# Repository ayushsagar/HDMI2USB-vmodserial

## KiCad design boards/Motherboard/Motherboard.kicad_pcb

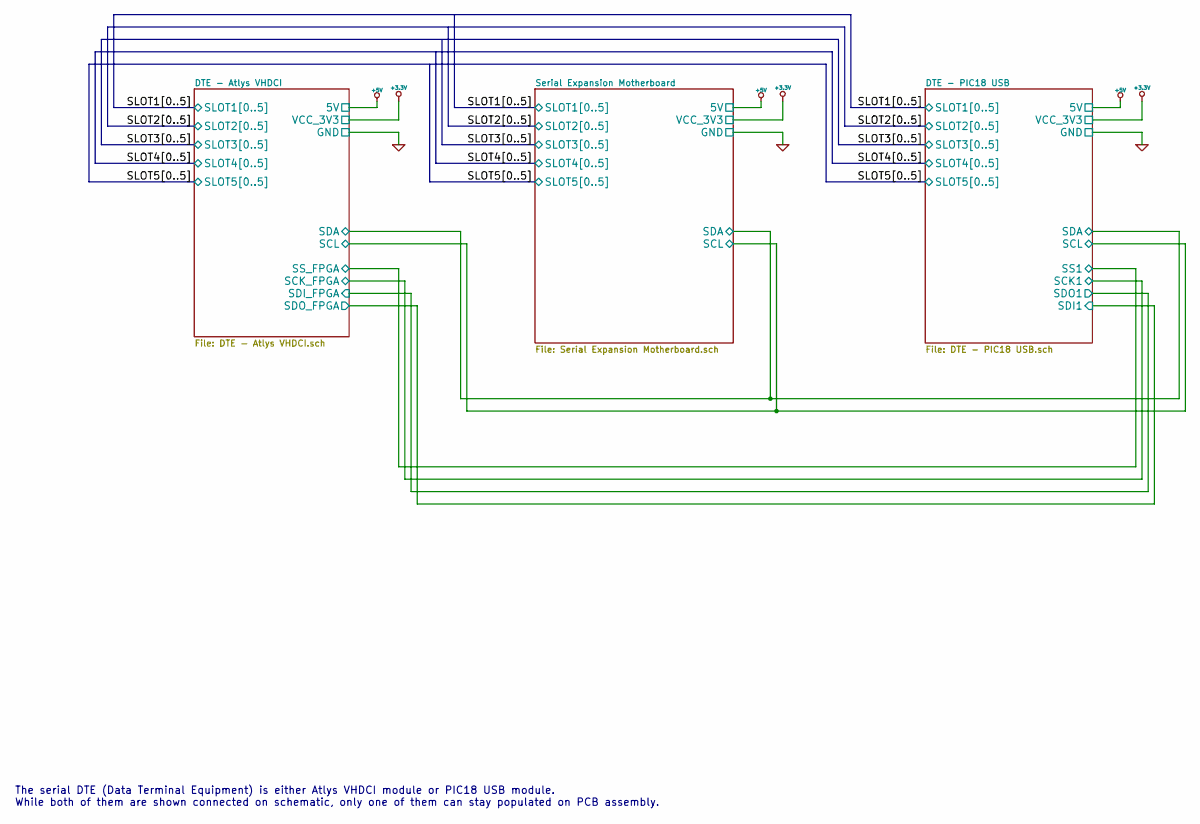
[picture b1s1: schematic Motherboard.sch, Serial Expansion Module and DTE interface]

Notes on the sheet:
The serial DTE (Data Terminal Equipment) is either Atlys VHDCI module or PIC18 USB module. While both of them are shown connected on schematic, only one of them can stay populated on PCB assembly.

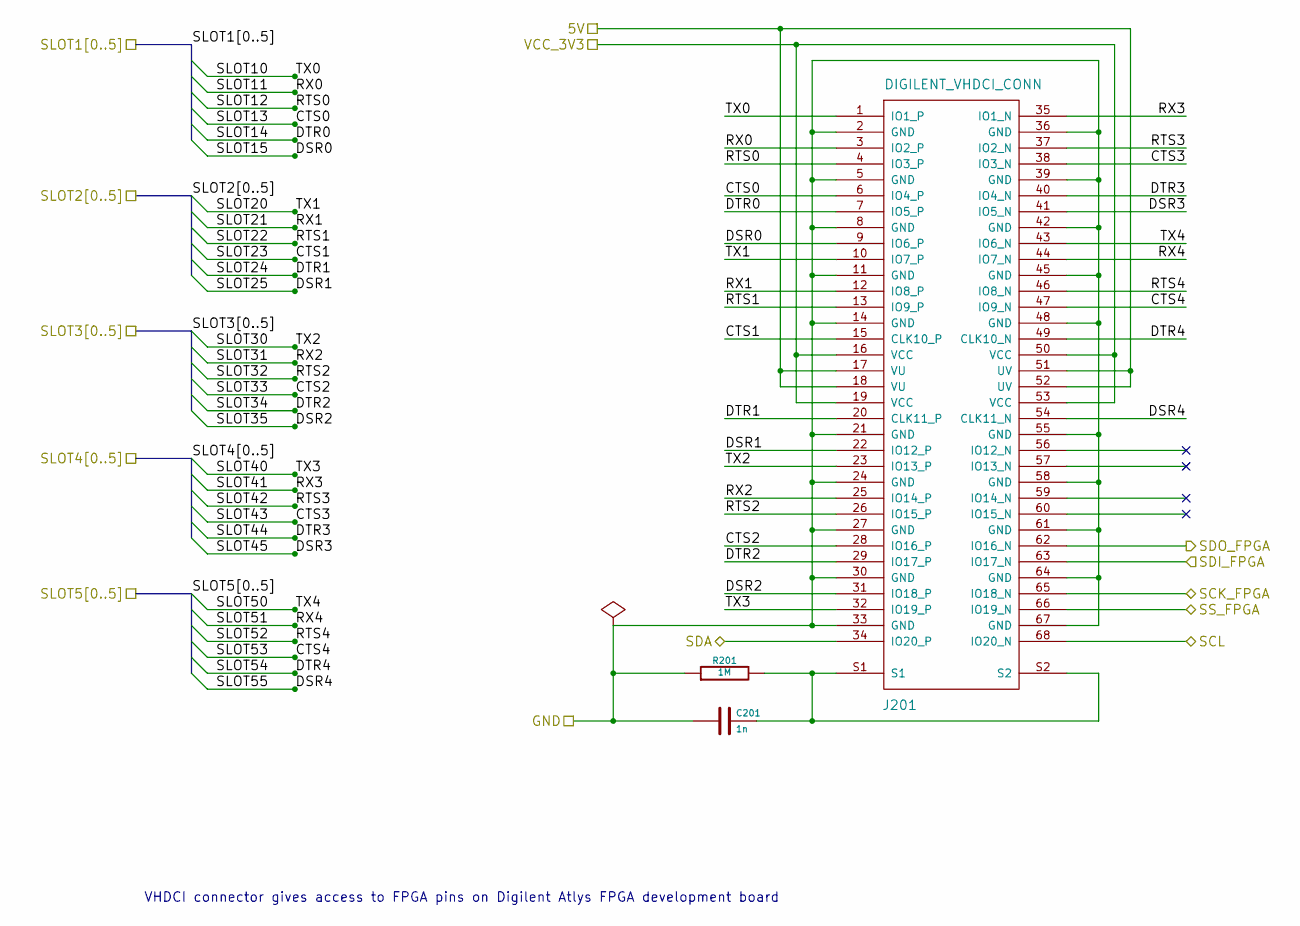
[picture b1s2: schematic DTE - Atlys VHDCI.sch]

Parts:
C201: 1n
J201: DIGILENT_VHDCI_CONN
R201: 1M

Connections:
+3.3V: J201.16 (VCC), J201.19 (VCC), J201.50 (VCC), J201.53 (VCC); also elsewhere on the board
+5V: J201.17 (VU), J201.18 (VU), J201.51 (UV), J201.52 (UV); also elsewhere on the board
/DTE - Atlys VHDCI/SCL: J201.68 (IO20_N); also elsewhere on the board
/DTE - Atlys VHDCI/SDA: J201.34 (IO20_P); also elsewhere on the board
/DTE - Atlys VHDCI/SDI_FPGA: J201.63 (IO17_N); also elsewhere on the board
/DTE - PIC18 USB/SCK1: J201.65 (IO18_N); also elsewhere on the board
/DTE - PIC18 USB/SDI1: J201.62 (IO16_N); also elsewhere on the board
/DTE - PIC18 USB/SS1: J201.66 (IO19_N); also elsewhere on the board
/Serial Expansion Motherboard/Data isolation/IN0_A: J201.1 (IO1_P); also elsewhere on the board
/Serial Expansion Motherboard/Data isolation/IN1_A: J201.4 (IO3_P); also elsewhere on the board
/Serial Expansion Motherboard/Data isolation/IN2_A: J201.7 (IO5_P); also elsewhere on the board
/Serial Expansion Motherboard/Data isolation/IN3_A: J201.10 (IO7_P); also elsewhere on the board
/Serial Expansion Motherboard/Data isolation/IN4_A: J201.13 (IO9_P); also elsewhere on the board
/Serial Expansion Motherboard/Data isolation/IN5_A: J201.20 (CLK11_P); also elsewhere on the board
/Serial Expansion Motherboard/Data isolation/IN6_A: J201.23 (IO13_P); also elsewhere on the board
/Serial Expansion Motherboard/Data isolation/IN7_A: J201.26 (IO15_P); also elsewhere on the board
/Serial Expansion Motherboard/Data isolation/IN8_A: J201.29 (IO17_P); also elsewhere on the board
/Serial Expansion Motherboard/Data isolation/IN9_A: J201.32 (IO19_P); also elsewhere on the board
/Serial Expansion Motherboard/Data isolation/IN10_A: J201.37 (IO2_N); also elsewhere on the board
/Serial Expansion Motherboard/Data isolation/IN11_A: J201.40 (IO4_N); also elsewhere on the board
/Serial Expansion Motherboard/Data isolation/IN12_A: J201.43 (IO6_N); also elsewhere on the board
/Serial Expansion Motherboard/Data isolation/IN13_A: J201.46 (IO8_N); also elsewhere on the board
/Serial Expansion Motherboard/Data isolation/IN14_A: J201.49 (CLK10_N); also elsewhere on the board
/Serial Expansion Motherboard/Data isolation/OUT0_A: J201.3 (IO2_P); also elsewhere on the board
/Serial Expansion Motherboard/Data isolation/OUT1_A: J201.6 (IO4_P); also elsewhere on the board
/Serial Expansion Motherboard/Data isolation/OUT2_A: J201.9 (IO6_P); also elsewhere on the board
/Serial Expansion Motherboard/Data isolation/OUT3_A: J201.12 (IO8_P); also elsewhere on the board
/Serial Expansion Motherboard/Data isolation/OUT4_A: J201.15 (CLK10_P); also elsewhere on the board
/Serial Expansion Motherboard/Data isolation/OUT5_A: J201.22 (IO12_P); also elsewhere on the board
/Serial Expansion Motherboard/Data isolation/OUT6_A: J201.25 (IO14_P); also elsewhere on the board
/Serial Expansion Motherboard/Data isolation/OUT7_A: J201.28 (IO16_P); also elsewhere on the board
/Serial Expansion Motherboard/Data isolation/OUT8_A: J201.31 (IO18_P); also elsewhere on the board
/Serial Expansion Motherboard/Data isolation/OUT9_A: J201.35 (IO1_N); also elsewhere on the board
/Serial Expansion Motherboard/Data isolation/OUT10_A: J201.38 (IO3_N); also elsewhere on the board
/Serial Expansion Motherboard/Data isolation/OUT11_A: J201.41 (IO5_N); also elsewhere on the board
/Serial Expansion Motherboard/Data isolation/OUT12_A: J201.44 (IO7_N); also elsewhere on the board
/Serial Expansion Motherboard/Data isolation/OUT13_A: J201.47 (IO9_N); also elsewhere on the board
/Serial Expansion Motherboard/Data isolation/OUT14_A: J201.54 (CLK11_N); also elsewhere on the board
GND: C201.1, J201.2 (GND), J201.5 (GND), J201.8 (GND), J201.11 (GND), J201.14 (GND), J201.21 (GND), J201.24 (GND), J201.27 (GND), J201.30 (GND), J201.33 (GND), J201.36 (GND), J201.39 (GND), J201.42 (GND), J201.45 (GND), J201.48 (GND), J201.55 (GND), J201.58 (GND), J201.61 (GND), J201.64 (GND), J201.67 (GND), R201.1; also elsewhere on the board
unnamed: C201.2, J201.S1, J201.S2, R201.2

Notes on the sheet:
VHDCI connector gives access to FPGA pins on Digilent Atlys FPGA development board

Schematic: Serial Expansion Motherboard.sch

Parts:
C401: 0.1u
R401, R402: 2.2k
R403: 50
U401: 24AA014

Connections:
+3.3V: R401.1, R402.1, R403.1; also elsewhere on the board
/DTE - Atlys VHDCI/SCL: R402.2, U401.5 (SDA); also elsewhere on the board
/DTE - Atlys VHDCI/SDA: R401.2, U401.6 (SCL); also elsewhere on the board
GND: C401.1, U401.1 (A0), U401.2 (A1), U401.3 (A2), U401.4 (GND), U401.7 (WP); also elsewhere on the board
unnamed: C401.2, R403.2, U401.8 (VCC)

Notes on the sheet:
Motherboard ID EEPROM address set to 0 (000) by shorting A0, A1 and A2 to ground.

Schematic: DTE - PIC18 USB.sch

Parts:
C613, C614: 22p
C615, C616, C618, C619, C620, C623: 0.1u
C617: 10u
C621: 4.7n
C622: 4.7u
D611, D612, D613: LED
DS11, DS12, DS21, DS22, DS31, DS32, DS41, DS42, DS51, DS52: LED
J601: USB
P601: ICSP
P602: SPI2
R619: 10K
R620, R621: 50
R640: 1M
R641: 0.47
R688, R689, R690: 680
R691: 0.10
RS11, RS12, RS21, RS22, RS31, RS32, RS41, RS42, RS51, RS52: 680
U607: PIC18F85J94
U608: AAT3221IGV-3.3-T1
X601: XTAL

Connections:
+3.3V: C616.1, C618.1, C619.1, C620.1, C623.1, P601.2, P602.1, R619.1, R691.2, U607.23 (VUSB3V3), U607.32 (VDD), U607.48 (VDD), U607.71 (VDD); also elsewhere on the board
+5V: C622.1, R641.2, U608.1 (IN), U608.3 (EN); also elsewhere on the board
/DTE - Atlys VHDCI/SCL: U607.44 (RC3/SCL1); also elsewhere on the board
/DTE - Atlys VHDCI/SDA: U607.45 (RC4/SDA1); also elsewhere on the board
/DTE - Atlys VHDCI/SDI_FPGA: U607.3 (RE1); also elsewhere on the board
/DTE - PIC18 USB/LED_P: R688.1, U607.72 (RD0)
/DTE - PIC18 USB/LED_Q: R689.1, U607.18 (RF2)
/DTE - PIC18 USB/LED_R: R690.1, U607.15 (RF5)
/DTE - PIC18 USB/PGC: P601.5, U607.52 (RB6/PGC)
/DTE - PIC18 USB/PGD: P601.4, U607.47 (RB7/PGD)
/DTE - PIC18 USB/SCK1: U607.6 (RG1); also elsewhere on the board
/DTE - PIC18 USB/SCK2_HEADER: P602.4, U607.7 (RG2)
/DTE - PIC18 USB/SDI1: U607.4 (RE0); also elsewhere on the board
/DTE - PIC18 USB/SDI2_HEADER: P602.3, U607.69 (RD1)
/DTE - PIC18 USB/SDO2_HEADER: P602.2, U607.10 (RG4)
/DTE - PIC18 USB/SLOT1_LED1: RS11.1, U607.36 (RC0)
/DTE - PIC18 USB/SLOT1_LED2: RS12.1, U607.35 (RC1)
/DTE - PIC18 USB/SLOT2_LED1: RS21.1, U607.43 (RC2)
/DTE - PIC18 USB/SLOT2_LED2: RS22.1, U607.46 (RC5)
/DTE - PIC18 USB/SLOT3_LED1: RS31.1, U607.37 (RC6)
/DTE - PIC18 USB/SLOT3_LED2: RS32.1, U607.38 (RC7)
/DTE - PIC18 USB/SLOT4_LED1: RS41.1, U607.14 (RF6)
/DTE - PIC18 USB/SLOT4_LED2: RS42.1, U607.13 (RF7)
/DTE - PIC18 USB/SLOT5_LED1: RS51.1, U607.20 (RH6)
/DTE - PIC18 USB/SLOT5_LED2: RS52.1, U607.19 (RH7)
/DTE - PIC18 USB/SS1: U607.5 (RG0); also elsewhere on the board
/DTE - PIC18 USB/SS2_HEADER: P602.5, U607.8 (RG3)
/Serial Expansion Motherboard/Data isolation/IN0_A: U607.28 (RA2); also elsewhere on the board
/Serial Expansion Motherboard/Data isolation/IN1_A: U607.34 (RA4); also elsewhere on the board
/Serial Expansion Motherboard/Data isolation/IN2_A: U607.30 (RA0); also elsewhere on the board
/Serial Expansion Motherboard/Data isolation/IN3_A: U607.55 (RB3); also elsewhere on the board
/Serial Expansion Motherboard/Data isolation/IN4_A: U607.54 (RB4); also elsewhere on the board
/Serial Expansion Motherboard/Data isolation/IN5_A: U607.58 (RB0); also elsewhere on the board
/Serial Expansion Motherboard/Data isolation/IN6_A: U607.65 (RD5/SDA2); also elsewhere on the board
/Serial Expansion Motherboard/Data isolation/IN7_A: U607.64 (RD6/SCL2); also elsewhere on the board
/Serial Expansion Motherboard/Data isolation/IN8_A: U607.68 (RD2); also elsewhere on the board
/Serial Expansion Motherboard/Data isolation/IN9_A: U607.75 (RE5); also elsewhere on the board
/Serial Expansion Motherboard/Data isolation/IN10_A: U607.74 (RE6); also elsewhere on the board
/Serial Expansion Motherboard/Data isolation/IN11_A: U607.78 (RE2); also elsewhere on the board
/Serial Expansion Motherboard/Data isolation/IN12_A: U607.1 (RH2); also elsewhere on the board
/Serial Expansion Motherboard/Data isolation/IN13_A: U607.22 (RH4); also elsewhere on the board
/Serial Expansion Motherboard/Data isolation/IN14_A: U607.79 (RH0); also elsewhere on the board
/Serial Expansion Motherboard/Data isolation/OUT0_A: U607.27 (RA3); also elsewhere on the board
/Serial Expansion Motherboard/Data isolation/OUT1_A: U607.33 (RA5); also elsewhere on the board
/Serial Expansion Motherboard/Data isolation/OUT2_A: U607.29 (RA1); also elsewhere on the board
/Serial Expansion Motherboard/Data isolation/OUT3_A: U607.56 (RB2); also elsewhere on the board
/Serial Expansion Motherboard/Data isolation/OUT4_A: U607.53 (RB5); also elsewhere on the board
/Serial Expansion Motherboard/Data isolation/OUT5_A: U607.57 (RB1); also elsewhere on the board
/Serial Expansion Motherboard/Data isolation/OUT6_A: U607.66 (RD4); also elsewhere on the board
/Serial Expansion Motherboard/Data isolation/OUT7_A: U607.63 (RD7); also elsewhere on the board
/Serial Expansion Motherboard/Data isolation/OUT8_A: U607.67 (RD3); also elsewhere on the board
/Serial Expansion Motherboard/Data isolation/OUT9_A: U607.76 (RE4); also elsewhere on the board
/Serial Expansion Motherboard/Data isolation/OUT10_A: U607.73 (RE7); also elsewhere on the board
/Serial Expansion Motherboard/Data isolation/OUT11_A: U607.77 (RE3); also elsewhere on the board
/Serial Expansion Motherboard/Data isolation/OUT12_A: U607.2 (RH3); also elsewhere on the board
/Serial Expansion Motherboard/Data isolation/OUT13_A: U607.21 (RH5); also elsewhere on the board
/Serial Expansion Motherboard/Data isolation/OUT14_A: U607.80 (RH1); also elsewhere on the board
GND: C613.1, C614.2, C615.2, C616.2, C617.2, C618.2, C619.2, C620.2, C621.2, C622.2, C623.2, D611.2 (K), D612.2 (K), D613.2 (K), DS11.2 (K), DS12.2 (K), DS21.2 (K), DS22.2 (K), DS31.2 (K), DS32.2 (K), DS41.2 (K), DS42.2 (K), DS51.2 (K), DS52.2 (K), J601.4 (GND), P601.3, P602.6, R640.2, U607.11 (VSS), U607.26 (AVSS), U607.31 (VSS), U607.51 (VSS), U607.70 (VSS), U608.2 (GND); also elsewhere on the board
unnamed: D613.1 (A), R690.2
unnamed: D612.1 (A), R689.2
unnamed: DS52.1 (A), RS52.2
unnamed: D611.1 (A), R688.2
unnamed: R621.1, U607.17 (D-/RF3)
unnamed: DS51.1 (A), RS51.2
unnamed: R620.1, U607.16 (D+/RF4)
unnamed: J601.3 (D+), R620.2
unnamed: J601.2 (D-), R621.2
unnamed: J601.1 (Vbus), R641.1
unnamed: R691.1, U608.5 (OUT)
unnamed: DS11.1 (A), RS11.2
unnamed: C621.1, J601.5 (Shield_1), J601.6 (Shield_2), R640.1
unnamed: DS12.1 (A), RS12.2
unnamed: P601.1, R619.2, U607.9 (~MCLR)
unnamed: C617.1, U607.12 (VCAP)
unnamed: C615.1, U607.25 (AVDD)
unnamed: DS41.1 (A), RS41.2
unnamed: C613.2, U607.50 (RA6/OSC1), X601.2
unnamed: C614.1, U607.49 (RA7/OSC2), X601.1
unnamed: DS42.1 (A), RS42.2
unnamed: DS32.1 (A), RS32.2
unnamed: DS31.1 (A), RS31.2
unnamed: DS22.1 (A), RS22.2
unnamed: DS21.1 (A), RS21.2

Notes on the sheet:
PIC18F85J94 MCU simulates production board for HDMI2USB as well as enables standalone operation using USB interface.
- First 4 serial ports use the 4 available hardware UARTs. Remaining serial ports need to be bitbanged - Crystal (and capactors) is optional. PIC18F85J94 has FRC internal clock, which is accurate enough to support USB 2.0 and UART.

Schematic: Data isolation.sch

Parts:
C601, C602, C603, C604, C605, C606, C607, C608, C609, C610, C611, C612: 0.1u
R601, R608, R615, R622, R629, R636, R643, R650, R657, R664, R671, R678: 50
R602, R603, R604, R605, R606, R607, R609, R610, R611, R612, R613, R614, R616, R617, R618, R623, R624, R625, R626, R627, R628, R630, R631, R632, R633, R634, R635, R637, R638, R639, R644, R645, R646, R647, R648, R649, R651, R652, R653, R654, R655, R656, R658, R659, R660, R665, R666, R667, R668, R669, R670, R672, R673, R674, R675, R676, R677, R679, R680, R681: 100
U601, U602, U603, U604: SI8660
U605, U606: SI8630/SI8660

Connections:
+3.3V: R601.1, R608.1, R615.1, R664.2, R671.2, R678.2; also elsewhere on the board
+5V_ISO: R622.2, R629.2, R636.2, R643.1, R650.1, R657.1; also elsewhere on the board
/Serial Expansion Motherboard/Data isolation/IN0_A: R602.1; also elsewhere on the board
/Serial Expansion Motherboard/Data isolation/IN0_B: R644.1; also elsewhere on the board
/Serial Expansion Motherboard/Data isolation/IN1_A: R603.1; also elsewhere on the board
/Serial Expansion Motherboard/Data isolation/IN2_A: R604.1; also elsewhere on the board
/Serial Expansion Motherboard/Data isolation/IN3_A: R605.1; also elsewhere on the board
/Serial Expansion Motherboard/Data isolation/IN3_B: R647.1; also elsewhere on the board
/Serial Expansion Motherboard/Data isolation/IN4_A: R606.1; also elsewhere on the board
/Serial Expansion Motherboard/Data isolation/IN5_A: R607.1; also elsewhere on the board
/Serial Expansion Motherboard/Data isolation/IN6_A: R609.1; also elsewhere on the board
/Serial Expansion Motherboard/Data isolation/IN6_B: R651.1; also elsewhere on the board
/Serial Expansion Motherboard/Data isolation/IN7_A: R610.1; also elsewhere on the board
/Serial Expansion Motherboard/Data isolation/IN8_A: R611.1; also elsewhere on the board
/Serial Expansion Motherboard/Data isolation/IN9_A: R612.1; also elsewhere on the board
/Serial Expansion Motherboard/Data isolation/IN9_B: R654.1; also elsewhere on the board
/Serial Expansion Motherboard/Data isolation/IN10_A: R613.1; also elsewhere on the board
/Serial Expansion Motherboard/Data isolation/IN11_A: R614.1; also elsewhere on the board
/Serial Expansion Motherboard/Data isolation/IN12_A: R616.1; also elsewhere on the board
/Serial Expansion Motherboard/Data isolation/IN12_B: R658.1; also elsewhere on the board
/Serial Expansion Motherboard/Data isolation/IN13_A: R617.1; also elsewhere on the board
/Serial Expansion Motherboard/Data isolation/IN14_A: R618.1; also elsewhere on the board
/Serial Expansion Motherboard/Data isolation/OUT0_A: R665.2; also elsewhere on the board
/Serial Expansion Motherboard/Data isolation/OUT0_B: R623.2; also elsewhere on the board
/Serial Expansion Motherboard/Data isolation/OUT1_A: R666.2; also elsewhere on the board
/Serial Expansion Motherboard/Data isolation/OUT1_B: R624.2; also elsewhere on the board
/Serial Expansion Motherboard/Data isolation/OUT2_A: R667.2; also elsewhere on the board
/Serial Expansion Motherboard/Data isolation/OUT3_A: R668.2; also elsewhere on the board
/Serial Expansion Motherboard/Data isolation/OUT3_B: R626.2; also elsewhere on the board
/Serial Expansion Motherboard/Data isolation/OUT4_A: R669.2; also elsewhere on the board
/Serial Expansion Motherboard/Data isolation/OUT4_B: R627.2; also elsewhere on the board
/Serial Expansion Motherboard/Data isolation/OUT5_A: R670.2; also elsewhere on the board
/Serial Expansion Motherboard/Data isolation/OUT6_A: R672.2; also elsewhere on the board
/Serial Expansion Motherboard/Data isolation/OUT6_B: R630.2; also elsewhere on the board
/Serial Expansion Motherboard/Data isolation/OUT7_A: R673.2; also elsewhere on the board
/Serial Expansion Motherboard/Data isolation/OUT8_A: R674.2; also elsewhere on the board
/Serial Expansion Motherboard/Data isolation/OUT9_A: R675.2; also elsewhere on the board
/Serial Expansion Motherboard/Data isolation/OUT9_B: R633.2; also elsewhere on the board
/Serial Expansion Motherboard/Data isolation/OUT10_A: R676.2; also elsewhere on the board
/Serial Expansion Motherboard/Data isolation/OUT10_B: R634.2; also elsewhere on the board
/Serial Expansion Motherboard/Data isolation/OUT11_A: R677.2; also elsewhere on the board
/Serial Expansion Motherboard/Data isolation/OUT12_A: R679.2; also elsewhere on the board
/Serial Expansion Motherboard/Data isolation/OUT12_B: R637.2; also elsewhere on the board
/Serial Expansion Motherboard/Data isolation/OUT13_A: R680.2; also elsewhere on the board
/Serial Expansion Motherboard/Data isolation/OUT13_B: R638.2; also elsewhere on the board
/Serial Expansion Motherboard/Data isolation/OUT14_A: R681.2; also elsewhere on the board
/Serial Expansion Motherboard/Daughterboard slots/CTS0_ISO: R645.1; also elsewhere on the board
/Serial Expansion Motherboard/Daughterboard slots/CTS1_ISO: R648.1; also elsewhere on the board
/Serial Expansion Motherboard/Daughterboard slots/CTS2_ISO: R631.2, R652.1; also elsewhere on the board
/Serial Expansion Motherboard/Daughterboard slots/CTS3_ISO: R655.1; also elsewhere on the board
/Serial Expansion Motherboard/Daughterboard slots/CTS4_ISO: R659.1; also elsewhere on the board
/Serial Expansion Motherboard/Daughterboard slots/DSR0_ISO: R646.1; also elsewhere on the board
/Serial Expansion Motherboard/Daughterboard slots/DSR1_ISO: R649.1; also elsewhere on the board
/Serial Expansion Motherboard/Daughterboard slots/DSR2_ISO: R653.1; also elsewhere on the board
/Serial Expansion Motherboard/Daughterboard slots/DSR3_ISO: R656.1; also elsewhere on the board
/Serial Expansion Motherboard/Daughterboard slots/DSR4_ISO: R660.1; also elsewhere on the board
/Serial Expansion Motherboard/Daughterboard slots/DTR0_ISO: R625.2; also elsewhere on the board
/Serial Expansion Motherboard/Daughterboard slots/DTR1_ISO: R628.2; also elsewhere on the board
/Serial Expansion Motherboard/Daughterboard slots/DTR2_ISO: R632.2; also elsewhere on the board
/Serial Expansion Motherboard/Daughterboard slots/DTR3_ISO: R635.2; also elsewhere on the board
/Serial Expansion Motherboard/Daughterboard slots/DTR4_ISO: R639.2; also elsewhere on the board
GND: C601.2, C602.2, C603.2, C610.2, C611.2, C612.2, U601.8 (GND1), U602.9 (GND2), U603.8 (GND1), U604.9 (GND2), U605.8 (GND1), U606.9 (GND2); also elsewhere on the board
GND_ISO: C604.2, C605.2, C606.2, C607.2, C608.2, C609.2, U601.9 (GND2), U602.8 (GND1), U603.9 (GND2), U604.8 (GND1), U605.9 (GND2), U606.8 (GND1); also elsewhere on the board
unnamed: R677.1, U604.10 (B6)
unnamed: R676.1, U604.11 (B5)
unnamed: R675.1, U604.12 (B4)
unnamed: R674.1, U604.13 (B3)
unnamed: R673.1, U604.14 (B2)
unnamed: R672.1, U604.15 (B1)
unnamed: R605.2, U601.5 (A4)
unnamed: R611.2, U603.4 (A3)
unnamed: R610.2, U603.3 (A2)
unnamed: R609.2, U603.2 (A1)
unnamed: R614.2, U603.7 (A6)
unnamed: R606.2, U601.6 (A5)
unnamed: R604.2, U601.4 (A3)
unnamed: R603.2, U601.3 (A2)
unnamed: R602.2, U601.2 (A1)
unnamed: R607.2, U601.7 (A6)
unnamed: R631.1, U603.14 (B2)
unnamed: R638.1, U605.13 (B3)
unnamed: R637.1, U605.14 (B2)
unnamed: R635.1, U603.10 (B6)
unnamed: R633.1, U603.12 (B4)
unnamed: R632.1, U603.13 (B3)
unnamed: R630.1, U603.15 (B1)
unnamed: R618.2, U605.5 (A4)
unnamed: R617.2, U605.4 (A3)
unnamed: R616.2, U605.3 (A2)
unnamed: R653.2, U604.4 (A3)
unnamed: R660.2, U606.5 (A4)
unnamed: R659.2, U606.4 (A3)
unnamed: R658.2, U606.3 (A2)
unnamed: R656.2, U604.7 (A6)
unnamed: R655.2, U604.6 (A5)
unnamed: R654.2, U604.5 (A4)
unnamed: R612.2, U603.5 (A4)
unnamed: R652.2, U604.3 (A2)
unnamed: R651.2, U604.2 (A1)
unnamed: R639.1, U605.12 (B4)
unnamed: R665.1, U602.15 (B1)
unnamed: R666.1, U602.14 (B2)
unnamed: R667.1, U602.13 (B3)
unnamed: R668.1, U602.12 (B4)
unnamed: R669.1, U602.11 (B5)
unnamed: R670.1, U602.10 (B6)
unnamed: R625.1, U601.13 (B3)
unnamed: R628.1, U601.10 (B6)
unnamed: R627.1, U601.11 (B5)
unnamed: R626.1, U601.12 (B4)
unnamed: R624.1, U601.14 (B2)
unnamed: R623.1, U601.15 (B1)
unnamed: R613.2, U603.6 (A5)
unnamed: R644.2, U602.2 (A1)
unnamed: R645.2, U602.3 (A2)
unnamed: R646.2, U602.4 (A3)
unnamed: R647.2, U602.5 (A4)
unnamed: R648.2, U602.6 (A5)
unnamed: R649.2, U602.7 (A6)
unnamed: R679.1, U606.14 (B2)
unnamed: R680.1, U606.13 (B3)
unnamed: R681.1, U606.12 (B4)
unnamed: R634.1, U603.11 (B5)
unnamed: C608.1, R650.2, U604.1 (VDD1)
unnamed: C612.1, R678.1, U606.16 (VDD2)
unnamed: C609.1, R657.2, U606.1 (VDD1)
unnamed: C607.1, R643.2, U602.1 (VDD1)
unnamed: C606.1, R636.1, U605.16 (VDD2)
unnamed: C610.1, R664.1, U602.16 (VDD2)
unnamed: C611.1, R671.1, U604.16 (VDD2)
unnamed: C604.1, R622.1, U601.16 (VDD2)
unnamed: C602.1, R608.2, U603.1 (VDD1)
unnamed: C601.1, R601.2, U601.1 (VDD1)
unnamed: C605.1, R629.1, U603.16 (VDD2)
unnamed: C603.1, R615.2, U605.1 (VDD1)

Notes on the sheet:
Postfix A refers to DTE side and postfix B refers to daughterboard side. e.g. IN12_A in an input from DTE side and OUT12_B is the output connected to daughterboard side.

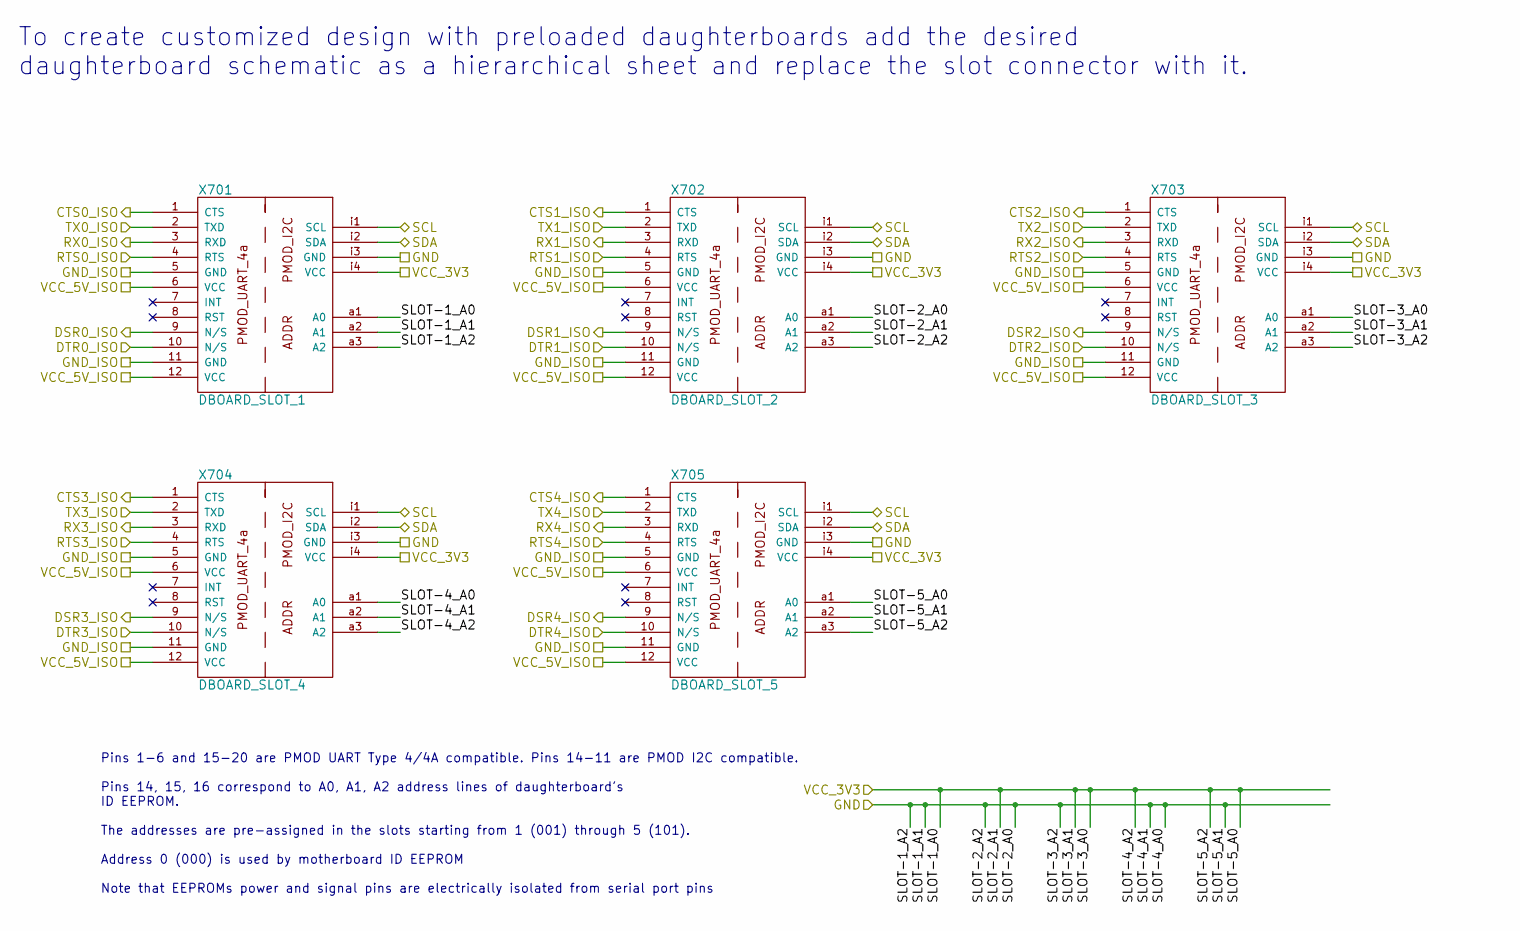
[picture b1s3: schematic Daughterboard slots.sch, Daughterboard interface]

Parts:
X701: DBOARD_SLOT_1
X702: DBOARD_SLOT_2
X703: DBOARD_SLOT_3
X704: DBOARD_SLOT_4
X705: DBOARD_SLOT_5

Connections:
+3.3V: X701.a1 (A0), X701.i4 (VCC), X702.a2 (A1), X702.i4 (VCC), X703.a1 (A0), X703.a2 (A1), X703.i4 (VCC), X704.a3 (A2), X704.i4 (VCC), X705.a1 (A0), X705.a3 (A2), X705.i4 (VCC); also elsewhere on the board
+5V_ISO: X701.6 (VCC), X701.12 (VCC), X702.6 (VCC), X702.12 (VCC), X703.6 (VCC), X703.12 (VCC), X704.6 (VCC), X704.12 (VCC), X705.6 (VCC), X705.12 (VCC); also elsewhere on the board
/DTE - Atlys VHDCI/SCL: X701.i2 (SDA), X702.i2 (SDA), X703.i2 (SDA), X704.i2 (SDA), X705.i2 (SDA); also elsewhere on the board
/DTE - Atlys VHDCI/SDA: X701.i1 (SCL), X702.i1 (SCL), X703.i1 (SCL), X704.i1 (SCL), X705.i1 (SCL); also elsewhere on the board
/Serial Expansion Motherboard/Data isolation/IN0_B: X701.3 (RXD); also elsewhere on the board
/Serial Expansion Motherboard/Data isolation/IN3_B: X702.3 (RXD); also elsewhere on the board
/Serial Expansion Motherboard/Data isolation/IN6_B: X703.3 (RXD); also elsewhere on the board
/Serial Expansion Motherboard/Data isolation/IN9_B: X704.3 (RXD); also elsewhere on the board
/Serial Expansion Motherboard/Data isolation/IN12_B: X705.3 (RXD); also elsewhere on the board
/Serial Expansion Motherboard/Data isolation/OUT0_B: X701.2 (TXD); also elsewhere on the board
/Serial Expansion Motherboard/Data isolation/OUT1_B: X701.4 (RTS); also elsewhere on the board
/Serial Expansion Motherboard/Data isolation/OUT3_B: X702.2 (TXD); also elsewhere on the board
/Serial Expansion Motherboard/Data isolation/OUT4_B: X702.4 (RTS); also elsewhere on the board
/Serial Expansion Motherboard/Data isolation/OUT6_B: X703.2 (TXD); also elsewhere on the board
/Serial Expansion Motherboard/Data isolation/OUT9_B: X704.2 (TXD); also elsewhere on the board
/Serial Expansion Motherboard/Data isolation/OUT10_B: X704.4 (RTS); also elsewhere on the board
/Serial Expansion Motherboard/Data isolation/OUT12_B: X705.2 (TXD); also elsewhere on the board
/Serial Expansion Motherboard/Data isolation/OUT13_B: X705.4 (RTS); also elsewhere on the board
/Serial Expansion Motherboard/Daughterboard slots/CTS0_ISO: X701.1 (CTS); also elsewhere on the board
/Serial Expansion Motherboard/Daughterboard slots/CTS1_ISO: X702.1 (CTS); also elsewhere on the board
/Serial Expansion Motherboard/Daughterboard slots/CTS2_ISO: X703.1 (CTS), X703.4 (RTS); also elsewhere on the board
/Serial Expansion Motherboard/Daughterboard slots/CTS3_ISO: X704.1 (CTS); also elsewhere on the board
/Serial Expansion Motherboard/Daughterboard slots/CTS4_ISO: X705.1 (CTS); also elsewhere on the board
/Serial Expansion Motherboard/Daughterboard slots/DSR0_ISO: X701.9 (N/S); also elsewhere on the board
/Serial Expansion Motherboard/Daughterboard slots/DSR1_ISO: X702.9 (N/S); also elsewhere on the board
/Serial Expansion Motherboard/Daughterboard slots/DSR2_ISO: X703.9 (N/S); also elsewhere on the board
/Serial Expansion Motherboard/Daughterboard slots/DSR3_ISO: X704.9 (N/S); also elsewhere on the board
/Serial Expansion Motherboard/Daughterboard slots/DSR4_ISO: X705.9 (N/S); also elsewhere on the board
/Serial Expansion Motherboard/Daughterboard slots/DTR0_ISO: X701.10 (N/S); also elsewhere on the board
/Serial Expansion Motherboard/Daughterboard slots/DTR1_ISO: X702.10 (N/S); also elsewhere on the board
/Serial Expansion Motherboard/Daughterboard slots/DTR2_ISO: X703.10 (N/S); also elsewhere on the board
/Serial Expansion Motherboard/Daughterboard slots/DTR3_ISO: X704.10 (N/S); also elsewhere on the board
/Serial Expansion Motherboard/Daughterboard slots/DTR4_ISO: X705.10 (N/S); also elsewhere on the board
GND: X701.a2 (A1), X701.a3 (A2), X701.i3 (GND), X702.a1 (A0), X702.a3 (A2), X702.i3 (GND), X703.a3 (A2), X703.i3 (GND), X704.a1 (A0), X704.a2 (A1), X704.i3 (GND), X705.a2 (A1), X705.i3 (GND); also elsewhere on the board
GND_ISO: X701.5 (GND), X701.11 (GND), X702.5 (GND), X702.11 (GND), X703.5 (GND), X703.11 (GND), X704.5 (GND), X704.11 (GND), X705.5 (GND), X705.11 (GND); also elsewhere on the board

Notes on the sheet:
To create customized design with preloaded daughterboards add the desired daughterboard schematic as a hierarchical sheet and replace the slot connector with it.
Pins 1-6 and 15-20 are PMOD UART Type 4/4A compatible. Pins 14-11 are PMOD I2C compatible. Pins 14, 15, 16 correspond to A0, A1, A2 address lines of daughterboard's ID EEPROM. The addresses are pre-assigned in the slots starting from 1 (001) through 5 (101). Address 0 (000) is used by motherboard I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

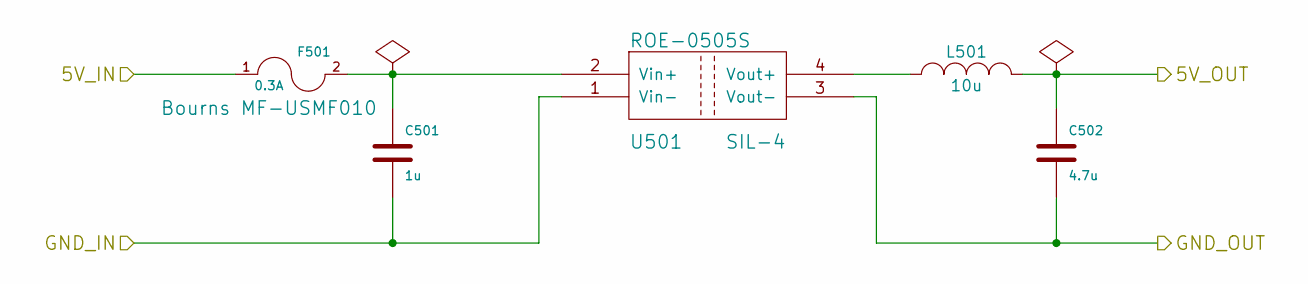
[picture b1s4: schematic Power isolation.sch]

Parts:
C501: 1u
C502: 4.7u
F501: 0.3A
L501: 10u
U501: ROE-0505S; SIL-4

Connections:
+5V: F501.1; also elsewhere on the board
+5V_ISO: C502.1, L501.2; also elsewhere on the board
GND: C501.2, U501.1 (Vin-); also elsewhere on the board
GND_ISO: C502.2, U501.3 (Vout-); also elsewhere on the board
unnamed: L501.1, U501.4 (Vout+)
unnamed: C501.1, F501.2, U501.2 (Vin+)

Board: 2 copper layers, 161 parts (104 on the bottom side), 190 nets, no tracks yet.

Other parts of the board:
Atlys_screw_hole: VAL**; Atlys_screw_hole
Atlys_screw_hole#2, Atlys_screw_hole#3, Atlys_screw_hole#4: VAL**; Atlys_screw_hole

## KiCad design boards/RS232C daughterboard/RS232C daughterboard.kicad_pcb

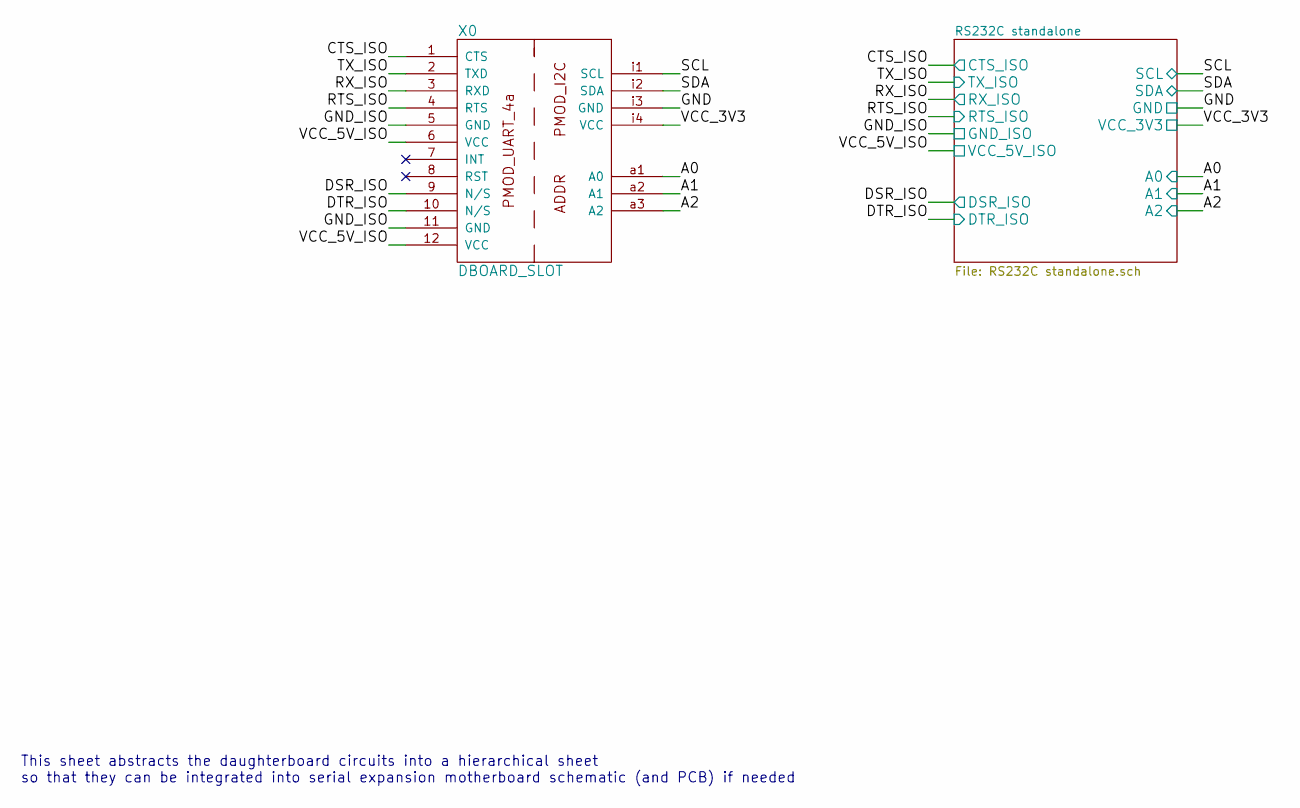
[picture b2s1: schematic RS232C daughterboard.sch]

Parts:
X0: DBOARD_SLOT

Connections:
unnamed: X0.5 (GND), X0.11 (GND)
unnamed: X0.6 (VCC), X0.12 (VCC)

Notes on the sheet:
This sheet abstracts the daughterboard circuits into a hierarchical sheet so that they can be integrated into serial expansion motherboard schematic (and PCB) if needed

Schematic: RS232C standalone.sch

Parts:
C201, C207, C208, C209, C210, C211, C212: 0.1u
D202: LED
J202: DB9
R202: 820
R203: 50
U202: 24AA014
U203: ISL83387E

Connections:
/RS232C standalone/A0: U202.1 (A0); also elsewhere on the board
/RS232C standalone/A1: U202.2 (A1); also elsewhere on the board
/RS232C standalone/A2: U202.3 (A2); also elsewhere on the board
/RS232C standalone/CTS_ISO: U203.13 (R2OUT); also elsewhere on the board
/RS232C standalone/C_CTS: J202.8, U203.17 (R2IN)
/RS232C standalone/C_DSR: J202.6, U203.16 (R3IN)
/RS232C standalone/C_DTR: J202.4, U203.19 (T3OUT)
/RS232C standalone/C_RTS: J202.7, U203.20 (T2OUT)
/RS232C standalone/C_RX: J202.2, U203.18 (R1IN)
/RS232C standalone/C_TX: J202.3, U203.21 (T1OUT)
/RS232C standalone/DSR_ISO: U203.12 (R3OUT); also elsewhere on the board
/RS232C standalone/DTR_ISO: U203.10 (T3IN); also elsewhere on the board
/RS232C standalone/GND: C201.1, U202.4 (GND), U202.7 (WP); also elsewhere on the board
/RS232C standalone/GND_ISO: C209.2, C210.2, C211.2, C212.2, D202.2 (K), J202.5, U203.11 (FORCEON), U203.22 (GND); also elsewhere on the board
/RS232C standalone/RTS_ISO: U203.8 (T2IN); also elsewhere on the board
/RS232C standalone/RX_ISO: U203.14 (R1OUT); also elsewhere on the board
/RS232C standalone/SCL: U202.6 (SCL); also elsewhere on the board
/RS232C standalone/SDA: U202.5 (SDA); also elsewhere on the board
/RS232C standalone/TX_ISO: U203.7 (T1IN); also elsewhere on the board
/RS232C standalone/VCC_3V3: R203.1; also elsewhere on the board
/RS232C standalone/VCC_5V_ISO: C211.1, C212.1, U203.15 (VL), U203.23 (VCC), U203.24 (~FORCEOFF); also elsewhere on the board
unnamed: C207.1, U203.1 (C1+)
unnamed: C207.2, U203.3 (C1-)
unnamed: C208.1, U203.4 (C2+)
unnamed: D202.1 (A), R202.1
unnamed: C208.2, U203.5 (C2-)
unnamed: R202.2, U203.9 (~INVALID)
unnamed: C210.1, U203.2 (V+)
unnamed: C209.1, U203.6 (V-)
unnamed: C201.2, R203.2, U202.8 (VCC)

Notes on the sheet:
DTE Serial DB9 pinout: 1 DCD <-- Data Carrier Detect 2 RXD <-- Receive Data 3 TXD --> Transmit Data 4 DTR --> Data Terminal Ready 5 GND --- System Ground 6 DSR <-- Data Set Ready 7 RTS --> Request to Send 8 CTS <-- Clear to Send 9 RI <-- Ring Indicator

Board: 2 copper layers, 14 parts (0 on the bottom side), 30 nets, no tracks yet.

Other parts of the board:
P0: HEADER; pin_array_10x2

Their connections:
/RS232C standalone/A0: P0.8; also elsewhere on the board
/RS232C standalone/A1: P0.9; also elsewhere on the board
/RS232C standalone/A2: P0.10; also elsewhere on the board
/RS232C standalone/CTS_ISO: P0.1; also elsewhere on the board
/RS232C standalone/DSR_ISO: P0.18; also elsewhere on the board
/RS232C standalone/DTR_ISO: P0.17; also elsewhere on the board
/RS232C standalone/GND: P0.12; also elsewhere on the board
/RS232C standalone/GND_ISO: P0.5, P0.16; also elsewhere on the board
/RS232C standalone/RTS_ISO: P0.4; also elsewhere on the board
/RS232C standalone/RX_ISO: P0.3; also elsewhere on the board
/RS232C standalone/SCL: P0.14; also elsewhere on the board
/RS232C standalone/SDA: P0.13; also elsewhere on the board
/RS232C standalone/TX_ISO: P0.2; also elsewhere on the board
/RS232C standalone/VCC_3V3: P0.11; also elsewhere on the board
/RS232C standalone/VCC_5V_ISO: P0.6; also elsewhere on the board
